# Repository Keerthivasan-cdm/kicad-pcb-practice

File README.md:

# KiCad PCB Design Practice: ESP32-C3 Boards (Play U SMD)

Two practice boards designed in **KiCad 9** (Sep–Oct 2026): a full ESP32-C3 + 9-axis IMU wearable board, then a compact 4-layer revision of the MCU and battery section.

---

## Board 1: Play U SMD (v1), ESP32-C3 + ICM-20948 Wearable Board

**2-layer · 94.6 × 37.6 mm · 1.6 mm FR-4 · 77 footprints · 38 vias**

### Hierarchical schematic (3 sheets)
| Sheet | Contents |
|---|---|
| `ESP32C3.kicad_sch` | ESP32-C3-WROOM-02 module, USB-C 2.0 receptacle (5.1 kΩ CC pull-downs), **USBLC6-2SC6** USB ESD protection, **PESD5V0L1ULD** TVS, **AP2112K-3.3** 3.3 V LDO, crystal, RESET/BOOT buttons |
| `ICM_20948.kicad_sch` | **ICM-20948** 9-axis IMU (QFN-24), **TLV70018** 1.8 V LDO for the IMU core, I2C/SPI/aux bus pull-ups, decoupling |
| `ucharging and battery provisition.kicad_sch` | **BQ25185** single-cell Li-ion charger with power-path, **MAX16054** push-button on/off controller, charge/status LEDs, battery connector, power switch |

### Layout
- 0201 resistors and 0805 capacitors, QFN-24 IMU, SOT-23 regulators.
- Ground pours on both layers; 0.1–0.2 mm signal tracks.
- Design rules: 0.2 mm pad-to-pad and pad-to-track clearance, 0.1 mm minimum track width.
- **Fabrication outputs:** Gerbers (F/B copper, mask, paste, silkscreen, Edge.Cuts), PTH/NPTH drill files, Gerber job file, **STEP 3D model**.

---

## Board 2: ESP32-C3 Compact Battery Board (v2)

**4-layer · 28.6 × 42.1 mm · 46 footprints · 22 vias**

- Same MCU, USB-C/ESD and BQ25185 charging + MAX16054 power circuits, condensed into a single sheet (`esp32c3-compact-v2/esp32c3.kicad_sch`).
- 0402 passives, BOOT and RESET buttons, charge/status LEDs.
- Copper zones for **GND, VBUS, SYS and 3.3 V** power distribution.
- 0.15–0.4 mm track widths: wider for power, narrower for signals.

---

## Repository layout
```
play-u-smd-v1/            Board 1: open ESP_32.kicad_pro in KiCad 9
  ESP_32.kicad_sch        root sheet
  ESP32C3.kicad_sch       MCU + USB-C + LDO sheet
  ICM_20948.kicad_sch     IMU sheet
  ucharging and battery provisition.kicad_sch   charger + power sheet
  ESP_32.kicad_pcb        2-layer layout
  gerbers/                Gerber, drill and job files (ready for JLCPCB/PCBWay)
  3d/                     STEP 3D models
esp32c3-compact-v2/       Board 2: open esp32c3.kicad_pro
```

## Tools
KiCad 9.0 (Eeschema, Pcbnew, 3D viewer), custom symbols and footprints for ICM-20948, BQ25185, TLV70018 and MAX16054.

## Author
**Keerthivasan J**, B.E. EEE, Sri Sairam Engineering College ([GitHub](https://github.com/Keerthivasan-cdm) · [LinkedIn](https://linkedin.com/in/keerthi-vasan-j-))

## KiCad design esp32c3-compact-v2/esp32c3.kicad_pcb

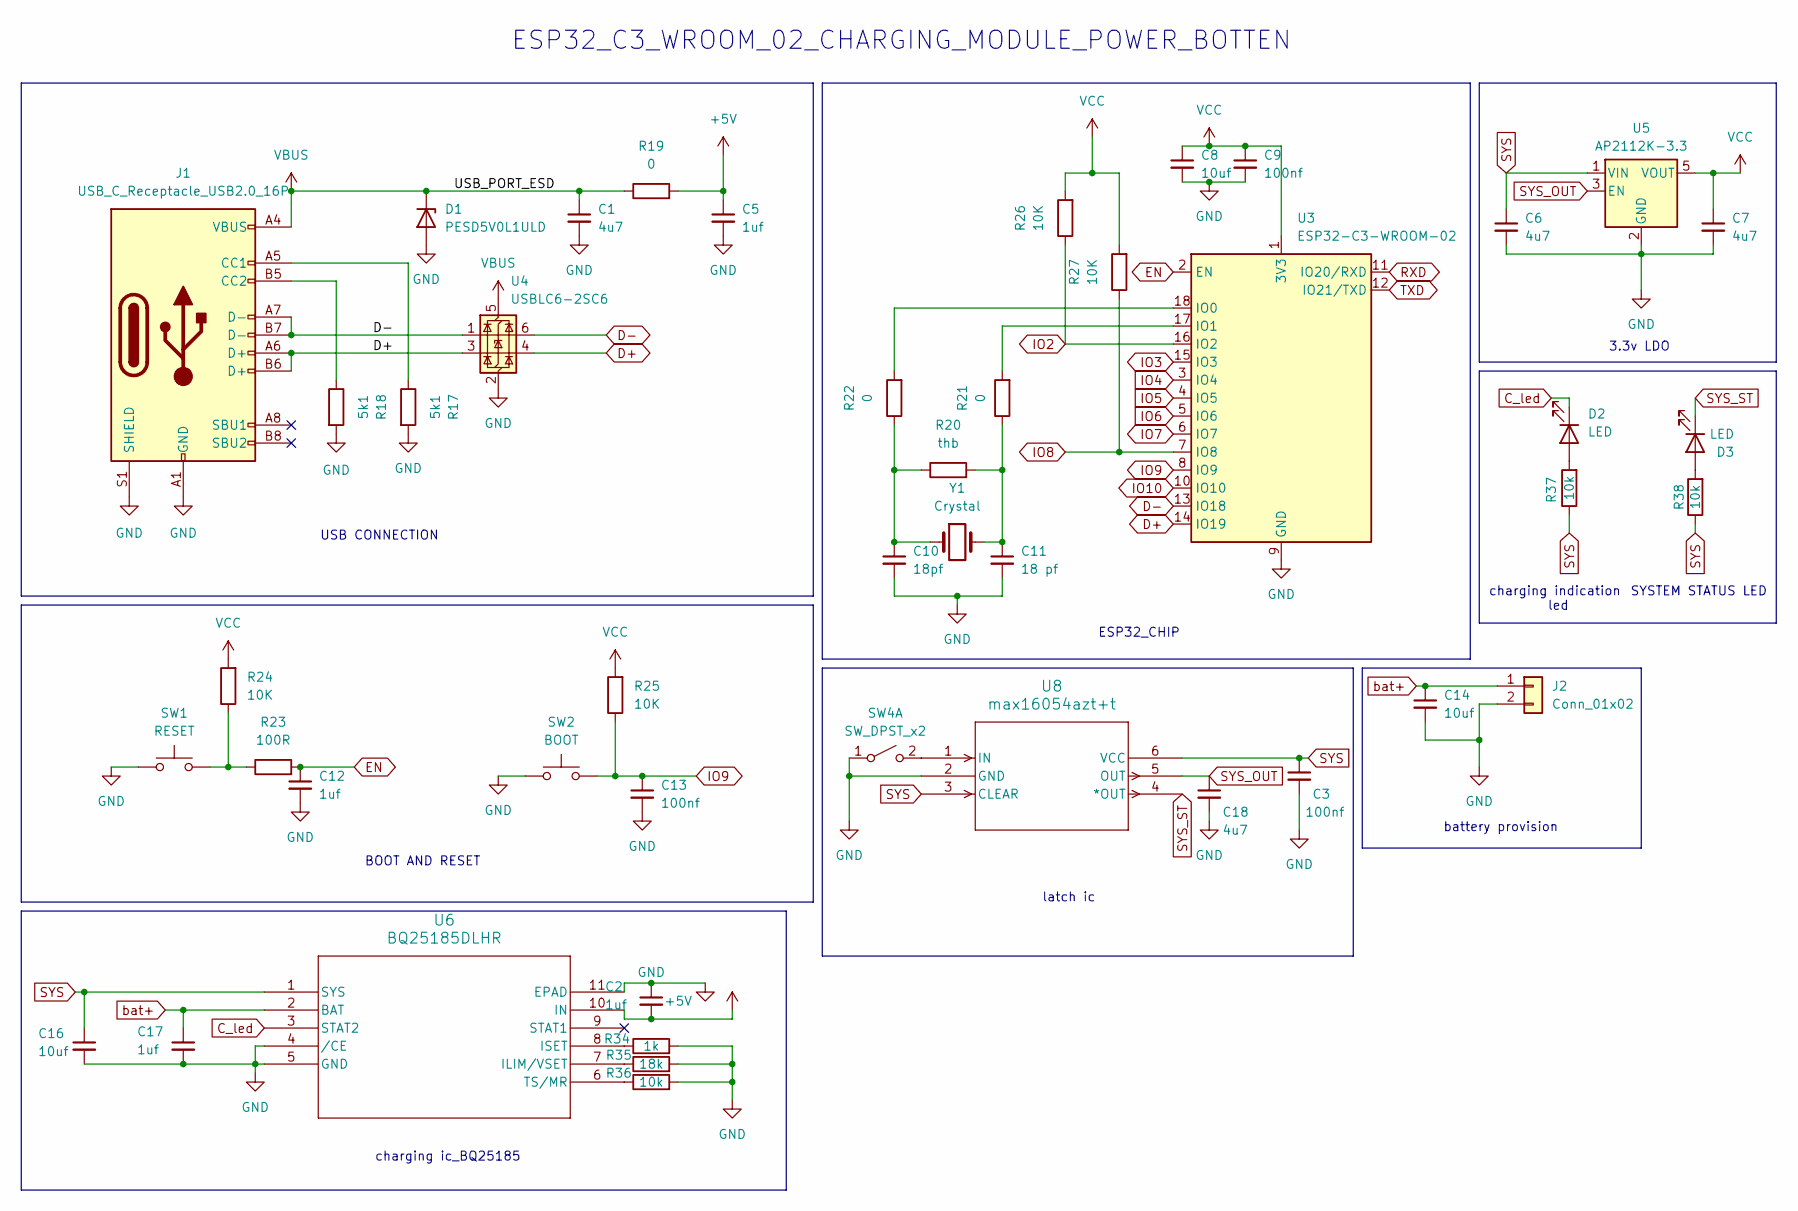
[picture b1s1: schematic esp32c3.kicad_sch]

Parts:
C1: 4u7; C_0402_1005Metric
C2, C5: 1uf; C_0603_1608Metric
C3: 100nf; C_0805_2012Metric
C6, C7, C18: 4u7; C_0805_2012Metric
C8, C14, C16: 10uf; C_0603_1608Metric
C9, C13: 100nf; C_0402_1005Metric
C10: 18pf; C_0402_1005Metric
C11: 18 pf; C_0402_1005Metric
C12, C17: 1uf; C_0805_2012Metric
D1: PESD5V0L1ULD; D_SOD-882D
D2, D3: LED; LED_0603_1608Metric
J1: USB_C_Receptacle_USB2.0_16P; USB_C_Receptacle_XKB_U262-16XN-4BVC11
J2: Conn_01x02; PinSocket_1x02_P2.54mm_Vertical
R17, R18: 5k1; R_0402_1005Metric
R19, R21, R22: 0; R_0402_1005Metric
R20: thb; R_0402_1005Metric
R23: 100R; R_0402_1005Metric
R24, R25, R26, R27: 10K; R_0402_1005Metric
R34: 1k; R_0402_1005Metric
R35: 18k; R_0402_1005Metric
R36, R37, R38: 10k; R_0402_1005Metric
SW1: RESET; SW_SPST_B3U-1000P
SW2: BOOT; SW_SPST_B3U-1000P
SW4: SW_DPST_x2; SW_SPST_B3U-1000P
U3: ESP32-C3-WROOM-02
U4: USBLC6-2SC6; SOT-23-6
U5: AP2112K-3.3; SOT-23-5
U6: BQ25185DLHR; BQ25185_FOOTPRINT
U8: max16054azt+t; 21-0114C_MXM-M
Y1: Crystal; Crystal_SMD_3215-2Pin_3.2x1.5mm

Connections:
+5V: C2.2, C5.1, R19.2, U6.10 (IN)
C_led: D2.1 (K), U6.3 (STAT2)
D+: J1.A6 (D+), J1.B6 (D+), U3.14 (IO19), U4.3 (I/O2), U4.4 (I/O2)
D-: J1.A7 (D-), J1.B7 (D-), U3.13 (IO18), U4.1 (I/O1), U4.6 (I/O1)
EN: C12.1, R23.2, U3.2 (EN)
GND: C1.2, C2.1, C3.2, C5.2, C6.2, C7.2, C8.2, C9.2, C10.2, C11.2, C12.2, C13.2, C14.2, C16.2, C17.2, C18.2, D1.2 (A), J1.A1 (GND), J1.A12 (GND), J1.B1 (GND), J1.B12 (GND), J1.S1 (SHIELD), J2.2, R17.2, R18.2, R34.2, R35.2, R36.2, SW1.1, SW2.1, SW4.1 (A), U3.9 (GND), U3.19 (GND), U4.2 (GND), U5.2 (GND), U6.4 (/CE), U6.5 (GND), U6.11 (EPAD), U8.2 (GND)
IO2: R26.1, U3.16 (IO2)
IO3: U3.15 (IO3)
IO4: U3.3 (IO4)
IO5: U3.4 (IO5)
IO6: U3.5 (IO6)
IO7: U3.6 (IO7)
IO8: R27.1, U3.7 (IO8)
IO9: C13.1, R25.1, SW2.2, U3.8 (IO9)
IO10: U3.10 (IO10)
unnamed: C10.1, R20.1, R22.1, Y1.1
unnamed: C11.1, R20.2, R21.1, Y1.2
unnamed: D2.2 (A), R37.2
unnamed: D3.2 (A), R38.2
unnamed: J1.A5 (CC1), R17.1
unnamed: J1.B5 (CC2), R18.1
unnamed: R23.1, R24.1, SW1.2
unnamed: SW4.2 (B), U8.1 (IN)
unnamed: R22.2, U3.18 (IO0)
unnamed: R21.2, U3.17 (IO1)
unnamed: R35.1, U6.7 (ILIM/VSET)
unnamed: R34.1, U6.8 (ISET)
unnamed: R36.1, U6.6 (TS/MR)
RXD: U3.11 (IO20/RXD)
SYS: C3.1, C6.1, C16.1, R37.1, R38.1, U5.1 (VIN), U6.1 (SYS), U8.3 (CLEAR), U8.6 (VCC)
SYS_OUT: C18.1, U5.3 (EN), U8.5 (OUT)
SYS_ST: D3.1 (K), U8.4 (*OUT)
TXD: U3.12 (IO21/TXD)
VBUS: C1.1, D1.1 (K), J1.A4 (VBUS), J1.A9 (VBUS), J1.B4 (VBUS), J1.B9 (VBUS), R19.1, U4.5 (VBUS)
VCC: C7.1, C8.1, C9.1, R24.2, R25.2, R26.2, R27.2, U3.1 (3V3), U5.5 (VOUT)
bat+: C14.1, C17.1, J2.1, U6.2 (BAT)

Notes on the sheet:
BOOT AND RESET
ESP32_CHIP
USB CONNECTION
charging ic_BQ25185
SYSTEM STATUS LED
charging indication led
ESP32_C3_WROOM_02_CHARGING_MODULE_POWER_BOTTEN
3.3v LDO
battery provision
latch ic

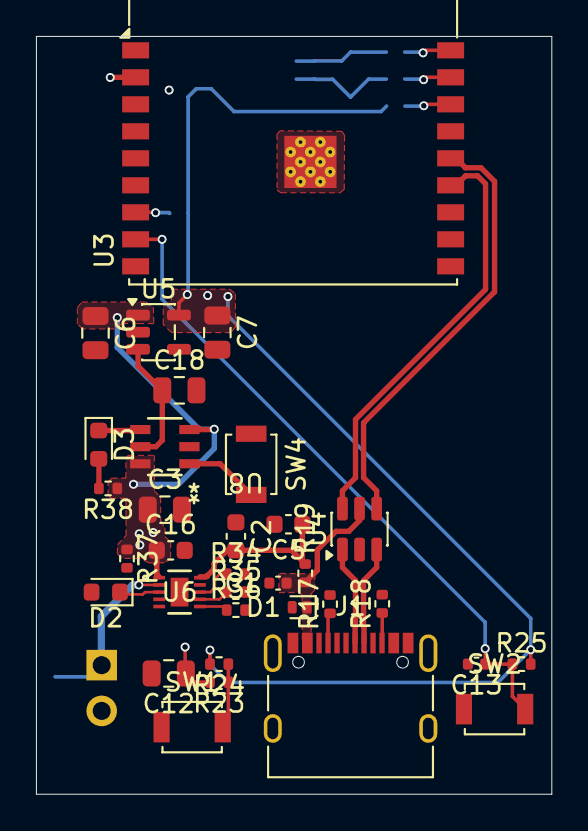
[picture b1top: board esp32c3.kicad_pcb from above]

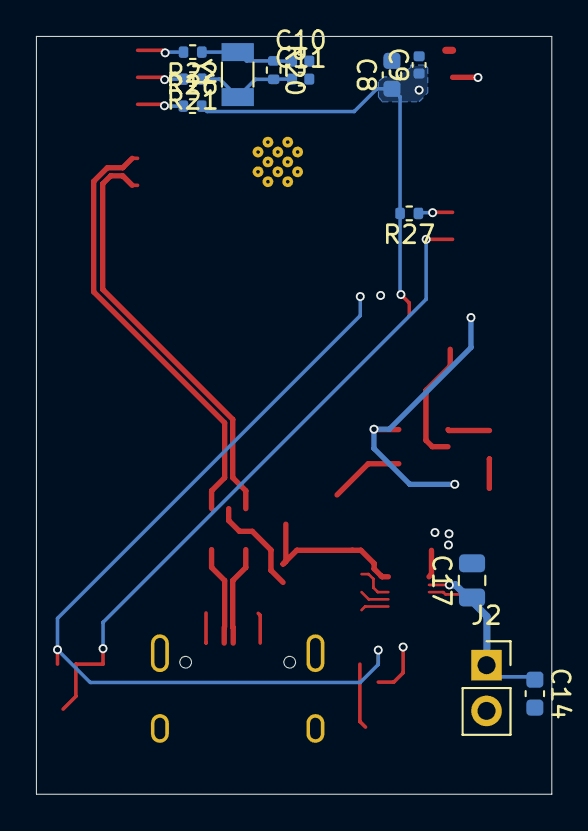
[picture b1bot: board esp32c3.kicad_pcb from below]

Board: 4 copper layers, 28.6 x 42.1 mm, 46 parts (13 on the bottom side), 28 nets.
